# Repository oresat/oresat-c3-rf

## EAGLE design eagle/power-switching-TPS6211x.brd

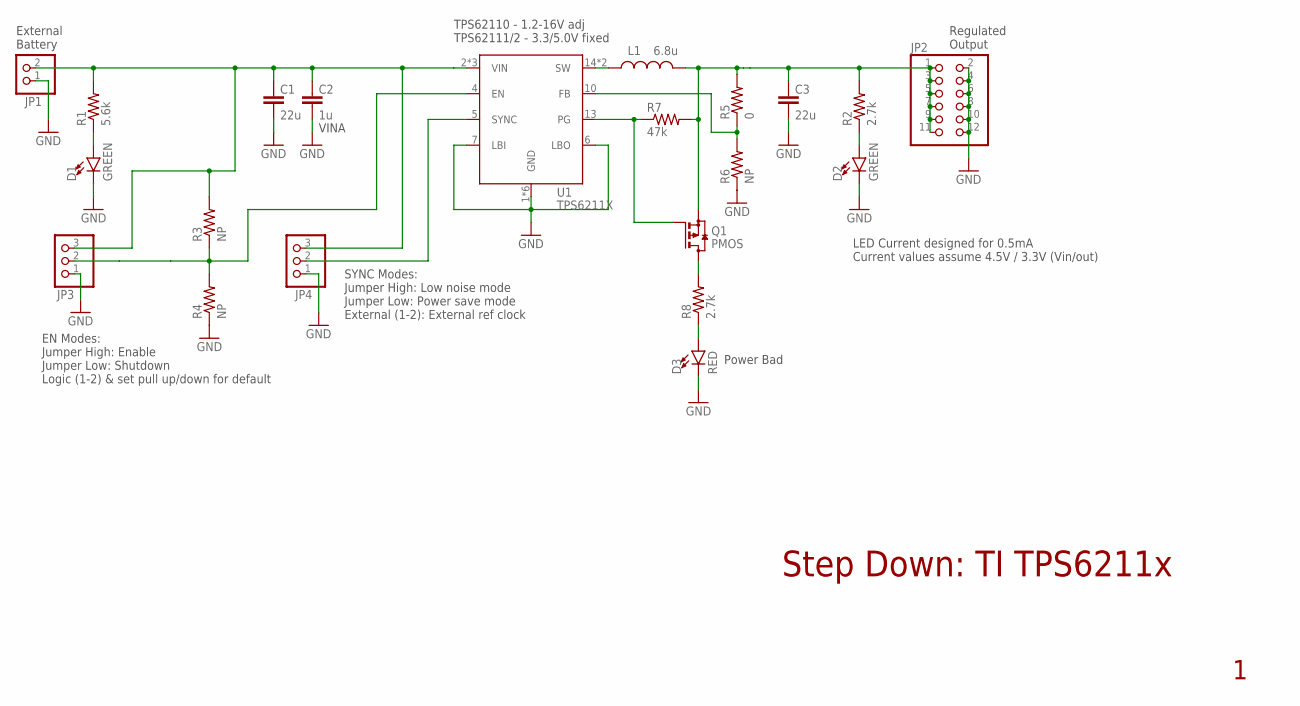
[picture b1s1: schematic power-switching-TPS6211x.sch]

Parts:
C1, C3: 22u; 1206-B
C2: 1u; .0603-B-NOSILK
D1, D2: GREEN; LED-0603
D3: RED; LED-0603
JP1: PINHD-1X2; 1X02
JP2: PINHD-2X6; 2X06
JP3, JP4: PINHD-1X3; 1X03
L1: 6.8u; ECS-MPI4040; MPN ECS-MPI4040R4-6R8-R
Q1: PMOS; SOT23
R1: 5.6k; .0603-B-NOSILK
R2, R8: 2.7k; .0603-B-NOSILK
R3, R4, R6: NP; .0402-B-NOSILK
R5: 0; .0402-B-NOSILK
R7: 47k; .0402-B-NOSILK
U1: TPS6211X; S-PVQFN-16

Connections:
+VIN: C1.1, C2.1, JP1.2, JP3.3, JP4.3, R1.2, R3.2, U1.2 (VIN), U1.3 (VIN), U1.8 (VIN)
+VOUT: C3.1, JP2.1, JP2.3, JP2.5, JP2.7, JP2.9, JP2.11, L1.2, Q1.2 (S), R2.2, R5.2, R7.2
+VOUT1: Q1.3 (D), R8.2
EN: JP3.2, R3.1, R4.2, U1.4 (EN)
FB: R5.1, R6.2, U1.10 (FB)
GND: C1.2, C2.2, C3.2, D1.C, D2.C, D3.C, JP1.1, JP2.2, JP2.4, JP2.6, JP2.8, JP2.10, JP2.12, JP3.1, JP4.1, R4.1, R6.1, U1.1 (GND), U1.6 (LBO), U1.7 (LBI), U1.9 (GND), U1.11 (GND), U1.12 (GND), U1.16 (GND), U1.PAD (GND)
unnamed: D3.A, R8.1
unnamed: D1.A, R1.1
unnamed: D2.A, R2.1
PG: Q1.1 (G), R7.1, U1.13 (PG)
SW: L1.1, U1.14 (SW), U1.15 (SW)
SYNC: JP4.2, U1.5 (SYNC)

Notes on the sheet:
Step Down: TI TPS6211x
Regulated Output
External Battery
SYNC Modes: Jumper High: Low noise mode Jumper Low: Power save mode External (1-2): External ref clock
EN Modes: Jumper High: Enable Jumper Low: Shutdown Logic (1-2) & set pull up/down for default
Power Bad
LED Current designed for 0.5mA Current values assume 4.5V / 3.3V (Vin/out)
VINA
TPS62110 - 1.2-16V adj TPS62111/2 - 3.3/5.0V fixed

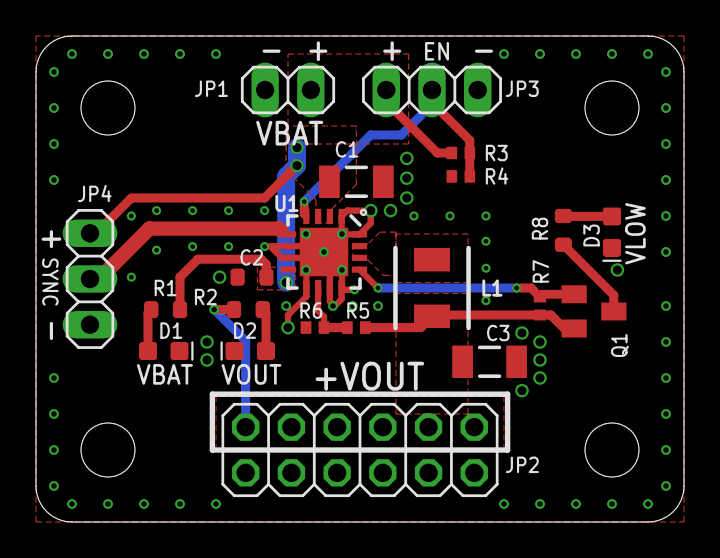
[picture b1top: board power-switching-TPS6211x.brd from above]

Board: 2 copper layers, 36.0 x 27.0 mm, 21 parts (0 on the bottom side), 12 nets.

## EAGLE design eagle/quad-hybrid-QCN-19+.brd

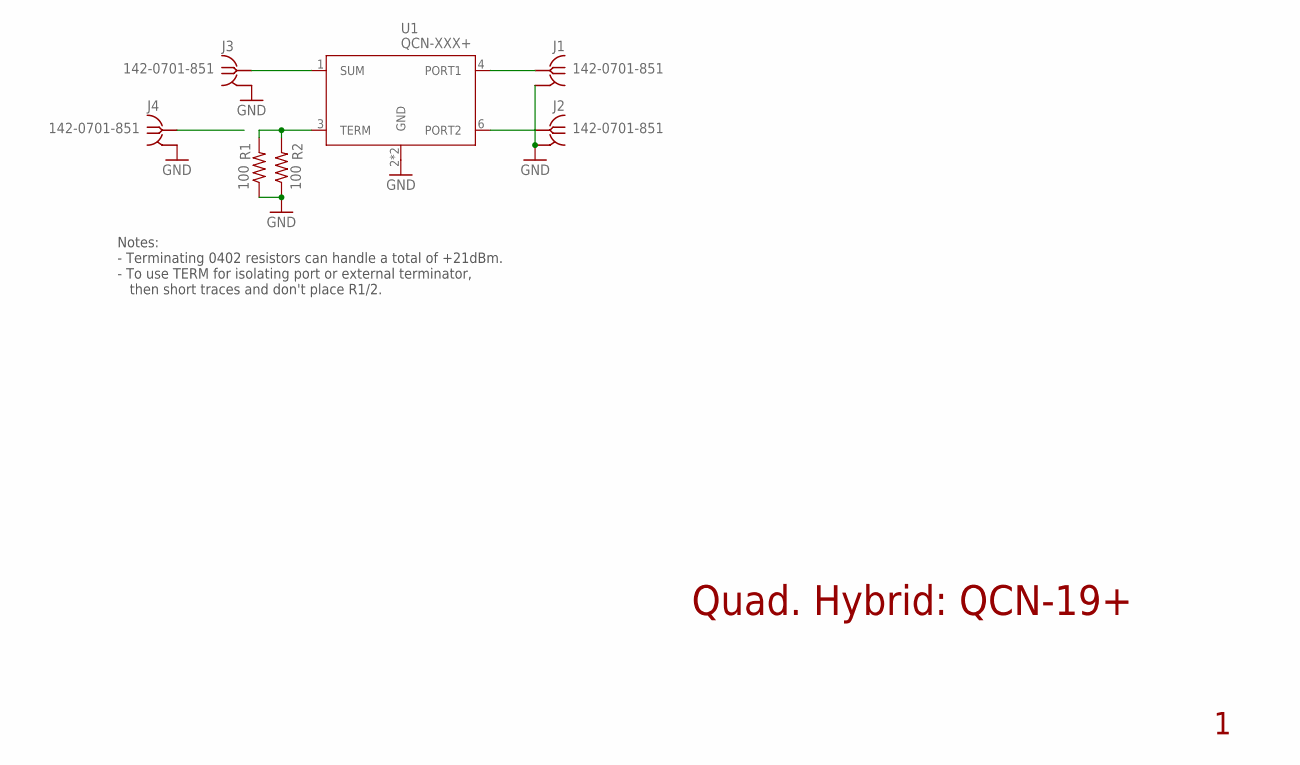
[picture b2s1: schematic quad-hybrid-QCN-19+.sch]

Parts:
J1, J2, J3, J4: 142-0701-851
R1, R2: 100; .0402-C-NOSILK
U1: QCN-XXX+

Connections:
GND: J1.GND1 (GND), J1.GND2 (GND), J1.GND3 (GND), J1.GND4 (GND), J2.GND1 (GND), J2.GND2 (GND), J2.GND3 (GND), J2.GND4 (GND), J3.GND1 (GND), J3.GND2 (GND), J3.GND3 (GND), J3.GND4 (GND), J4.GND1 (GND), J4.GND2 (GND), J4.GND3 (GND), J4.GND4 (GND), R1.1, R2.1, U1.2 (GND), U1.5 (GND)
ISO: J4.RF1 (RF)
P1: J1.RF1 (RF), U1.4 (PORT1)
P2: J2.RF1 (RF), U1.6 (PORT2)
SUM: J3.RF1 (RF), U1.1 (SUM)
TERM: R1.2, R2.2, U1.3 (TERM)

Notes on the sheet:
Quad. Hybrid: QCN-19+
Notes: - Terminating 0402 resistors can handle a total of +21dBm. - To use TERM for isolating port or external terminator, then short traces and don't place R1/2.

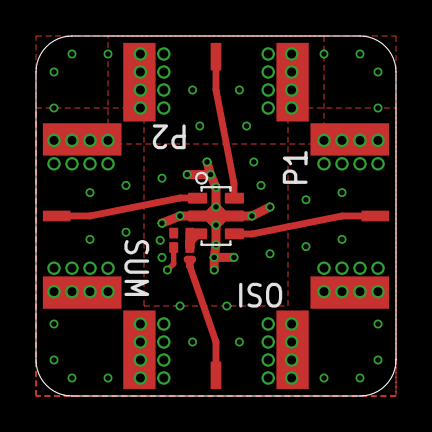
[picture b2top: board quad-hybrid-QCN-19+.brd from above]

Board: 4 copper layers, 20.0 x 20.0 mm, 7 parts (0 on the bottom side), 5 nets.

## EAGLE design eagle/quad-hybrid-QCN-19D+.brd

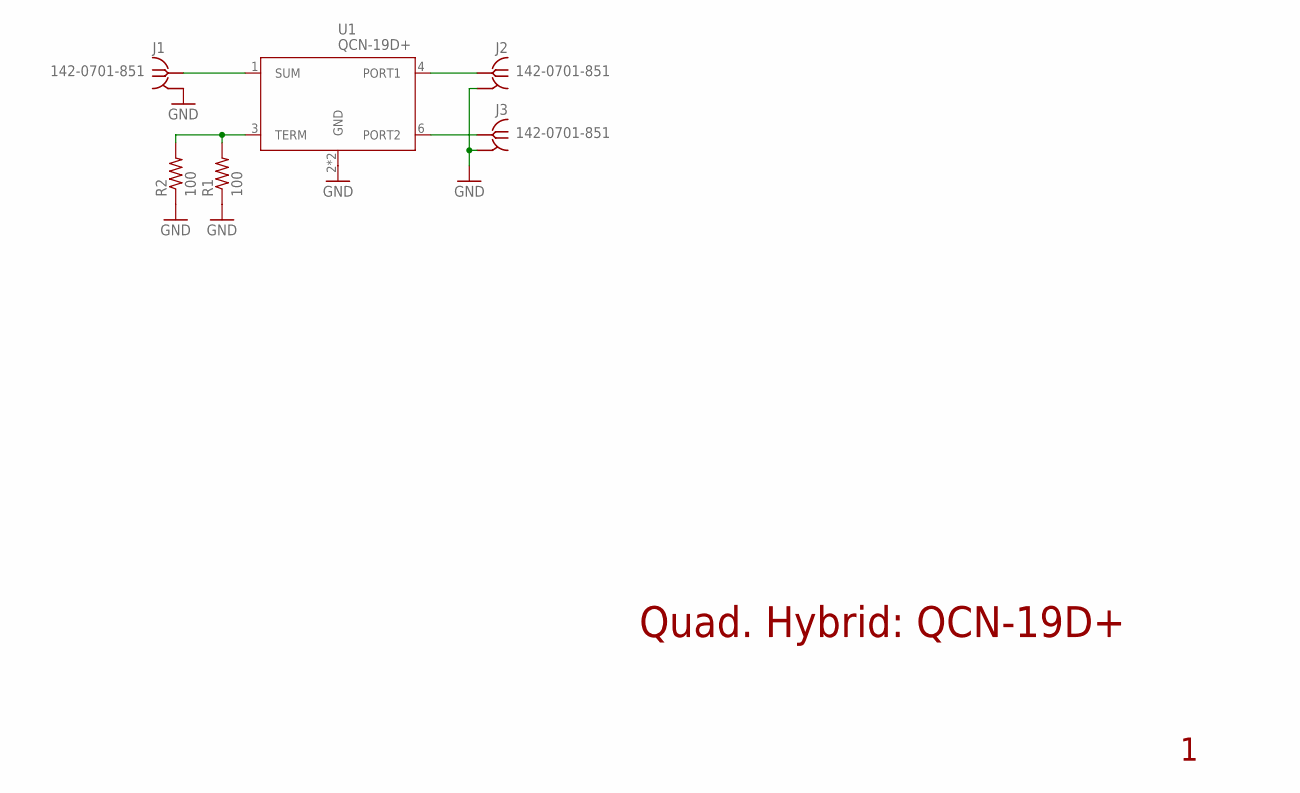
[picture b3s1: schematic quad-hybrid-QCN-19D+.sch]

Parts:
J1, J2, J3: 142-0701-851
R1, R2: 100; .0402-C-NOSILK
U1: QCN-19D+

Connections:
GND: J1.GND1 (GND), J1.GND2 (GND), J1.GND3 (GND), J1.GND4 (GND), J2.GND1 (GND), J2.GND2 (GND), J2.GND3 (GND), J2.GND4 (GND), J3.GND1 (GND), J3.GND2 (GND), J3.GND3 (GND), J3.GND4 (GND), R1.1, R2.1, U1.2 (GND), U1.5 (GND)
PORT1: J2.RF1 (RF), U1.4 (PORT1)
PORT2: J3.RF1 (RF), U1.6 (PORT2)
SUM: J1.RF1 (RF), U1.1 (SUM)
TERM: R1.2, R2.2, U1.3 (TERM)

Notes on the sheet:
Quad. Hybrid: QCN-19D+

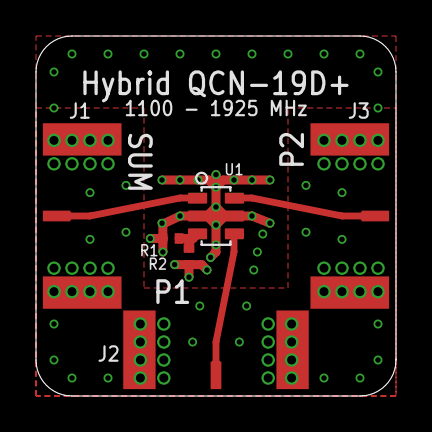
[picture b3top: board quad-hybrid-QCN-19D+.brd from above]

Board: 4 copper layers, 20.0 x 20.0 mm, 6 parts (0 on the bottom side), 5 nets.

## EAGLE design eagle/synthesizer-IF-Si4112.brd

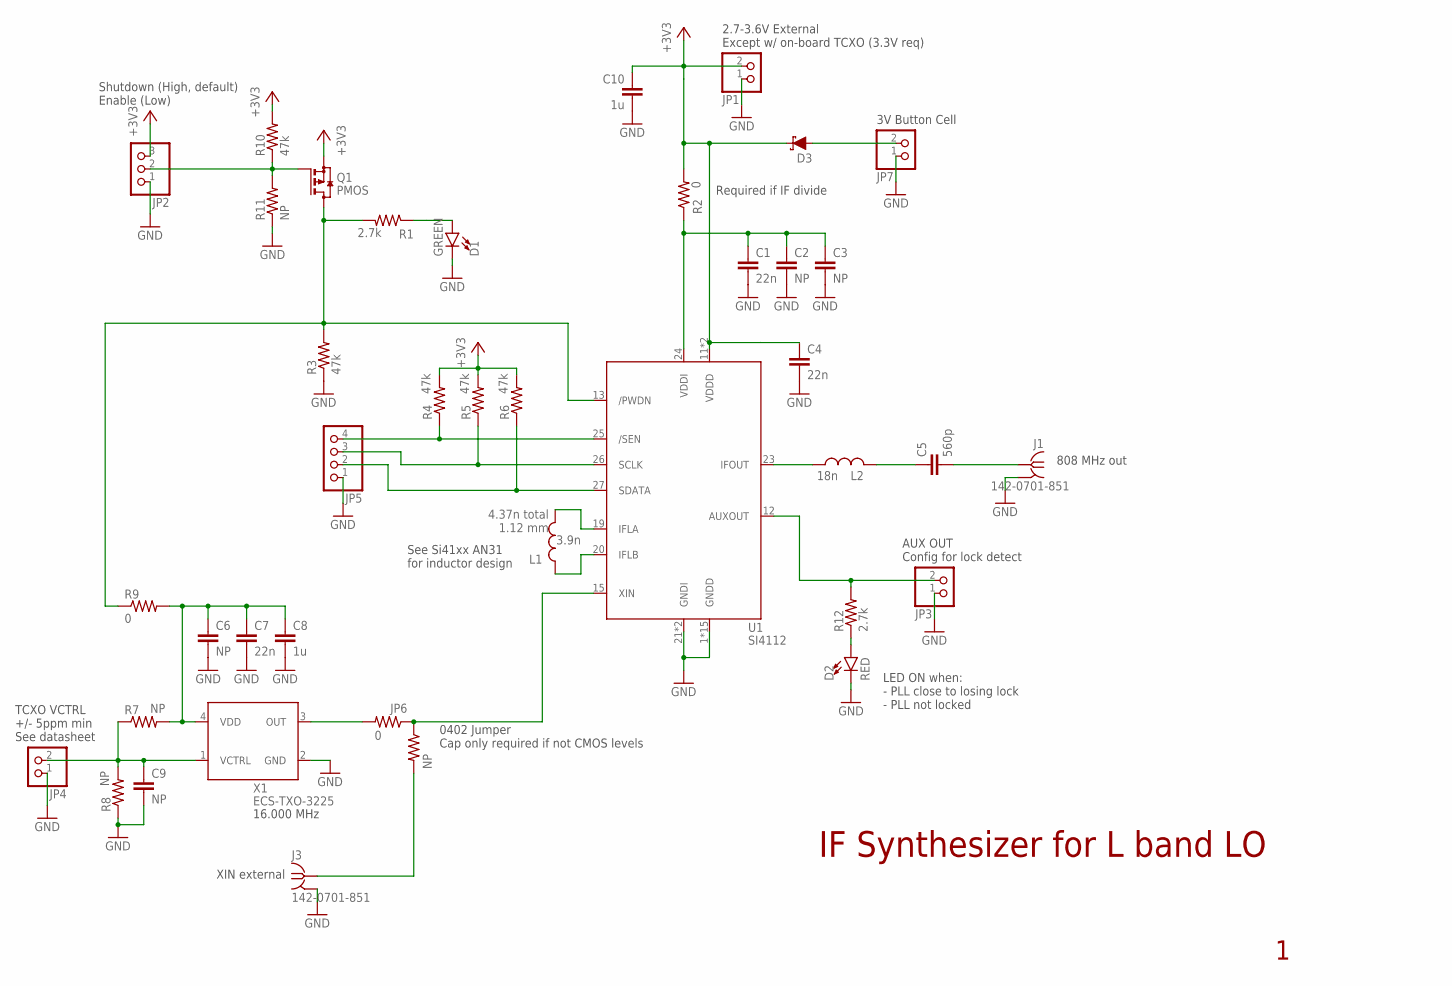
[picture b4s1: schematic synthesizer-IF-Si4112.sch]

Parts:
C1, C4, C7: 22n; .0603-B-NOSILK
C2, C3, C6, C9: NP; .0603-B-NOSILK
C5: 560p; .0402-B-NOSILK
C8, C10: 1u; .0603-B-NOSILK
D1: GREEN; LED-0603
D2: RED; LED-0603
D3: 120mA/40V/370mV; SOD-523
J1, J3: 142-0701-851
JP1, JP3, JP4, JP7: PINHD-1X2; 1X02
JP2: PINHD-1X3; 1X03
JP5: PINHD-1X4; 1X04
JP6: 0; .0402-B-NOSILK
L1: 3.9n; .0402-C-NOSILK
L2: 18n; .0402-B-NOSILK
Q1: PMOS; SOT23
R1, R12: 2.7k; .0603-B-NOSILK
R2, R9: 0; .0603-B-NOSILK
R3, R4, R5, R6, R10: 47k; .0402-B-NOSILK
R7, R8: NP; .0603-B-NOSILK
R11, R99: NP; .0402-B-NOSILK
U1: SI4112; QFN28-5X5-WITH-CENTER-PAD
X1: ECS-TXO-3225; 3.2X2.5

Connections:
+3V3: C4.1, C10.1, D3.C, JP1.2, JP2.3, Q1.2 (S), R2.2, R4.2, R5.2, R6.2, R10.2, U1.11 (VDDD), U1.17 (VDDD)
/SEN: JP5.4, R4.1, U1.25 (/SEN)
AUX: JP3.2, R12.2, U1.12 (AUXOUT)
GND: C1.2, C2.2, C3.2, C4.2, C6.2, C7.2, C8.2, C9.2, C10.2, D1.C, D2.C, J1.GND1 (GND), J1.GND2 (GND), J1.GND3 (GND), J1.GND4 (GND), J3.GND1 (GND), J3.GND2 (GND), J3.GND3 (GND), J3.GND4 (GND), JP1.1, JP2.1, JP3.1, JP4.1, JP5.1, JP7.1, R3.1, R8.1, R11.1, U1.1 (GNDD), U1.2 (GNDD), U1.3 (GNDD), U1.4 (GNDD), U1.5 (GNDD), U1.6 (GNDD), U1.7 (GNDD), U1.8 (GNDD), U1.9 (GNDD), U1.10 (GNDD), U1.14 (GNDD), U1.16 (GNDD), U1.18 (GNDD), U1.21 (GNDI), U1.22 (GNDI), U1.28 (GNDD), U1.PAD (GNDD), X1.2 (GND)
IF_OUT: C5.2, J1.RF1 (RF)
unnamed: D3.A, JP7.2
unnamed: L1.2, U1.19 (IFLA)
unnamed: L1.1, U1.20 (IFLB)
unnamed: JP2.2, Q1.1 (G), R10.1, R11.2
unnamed: Q1.3 (D), R1.2, R3.2, R9.1, U1.13 (/PWDN)
unnamed: JP6.2, X1.3 (OUT)
unnamed: C6.1, C7.1, C8.1, R7.2, R9.2, X1.4 (VDD)
unnamed: C5.1, L2.2
unnamed: D1.A, R1.1
unnamed: D2.A, R12.1
unnamed: L2.1, U1.23 (IFOUT)
unnamed: C1.1, C2.1, C3.1, R2.1, U1.24 (VDDI)
REF_IN: J3.RF1 (RF), R99.2
SCLK: JP5.3, R5.1, U1.26 (SCLK)
SDATA: JP5.2, R6.1, U1.27 (SDATA)
VCTRL: C9.1, JP4.2, R7.1, R8.2, X1.1 (VCTRL)
XIN: JP6.1, R99.1, U1.15 (XIN)

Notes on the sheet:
IF Synthesizer for L band LO
4.37n total 1.12 mm
Required if IF divide
808 MHz out
XIN external
2.7-3.6V External Except w/ on-board TCXO (3.3V req)
16.000 MHz
0402 Jumper Cap only required if not CMOS levels
Shutdown (High, default) Enable (Low)
TCXO VCTRL +/- 5ppm min See datasheet
AUX OUT Config for lock detect
LED ON when: - PLL close to losing lock - PLL not locked
3V Button Cell
See Si41xx AN31 for inductor design

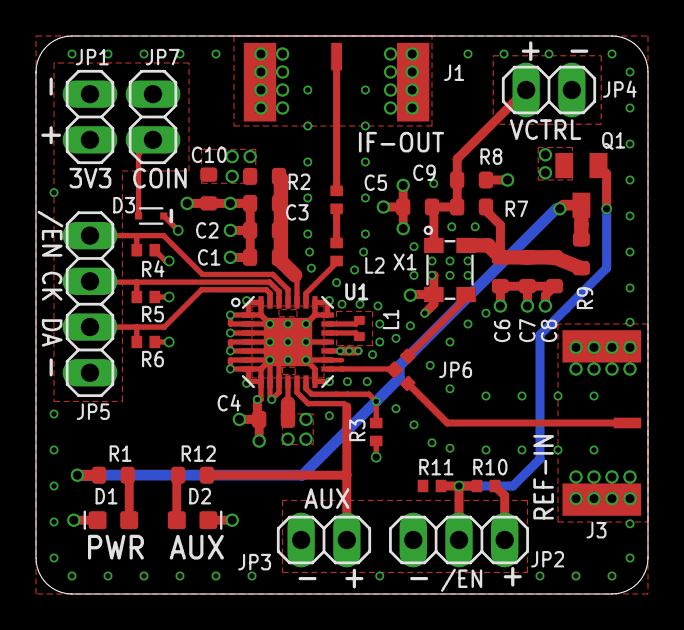
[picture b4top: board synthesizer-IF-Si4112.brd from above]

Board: 4 copper layers, 34.0 x 31.0 mm, 40 parts (0 on the bottom side), 22 nets.

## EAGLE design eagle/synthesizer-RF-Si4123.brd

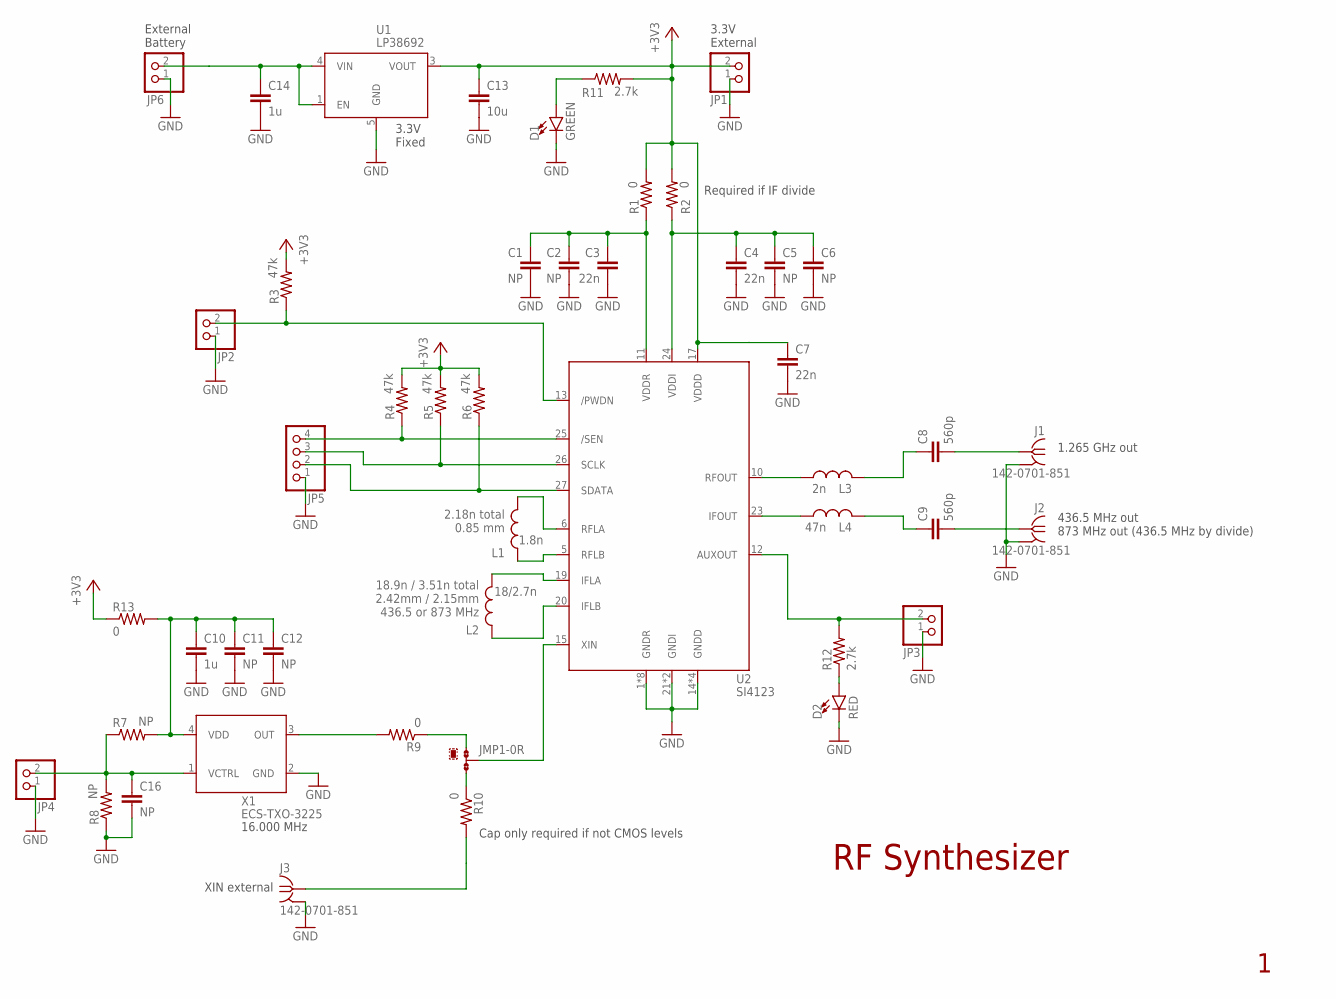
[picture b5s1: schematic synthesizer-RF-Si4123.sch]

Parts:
C1, C2, C5, C6, C11, C12, C16: NP; .0603-B-NOSILK
C3, C4, C7: 22n; .0603-B-NOSILK
C8, C9: 560p; .0402-B-NOSILK
C10, C14: 1u; .0603-B-NOSILK
C13: 10u; .0805-B-NOSILK
D1: GREEN; LED-0603
D2: RED; LED-0603
J1, J2, J3: 142-0701-851
JMP1: 0R-JUMPA; A0R-JMP
JP1, JP2, JP3, JP4, JP6: PINHD-1X2; 1X02
JP5: PINHD-1X4; 1X04
L1: 1.8n; .0402-C-NOSILK
L2: 18/2.7n; .0402-C-NOSILK
L3: 2n; .0402-B-NOSILK
L4: 47n; .0402-B-NOSILK
R1, R2, R13: 0; .0603-B-NOSILK
R3, R4, R5, R6: 47k; .0402-B-NOSILK
R7, R8: NP; .0603-B-NOSILK
R9, R10: 0; .0402-B-NOSILK
R11, R12: 2.7k; .0603-B-NOSILK
U1: LP38692; SOT223-5
U2: SI4123; QFN28-5X5-WITH-CENTER-PAD
X1: ECS-TXO-3225; 3.2X2.5

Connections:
+3V3: C7.1, C13.1, JP1.2, R1.2, R2.2, R3.2, R4.2, R5.2, R6.2, R11.2, R13.1, U1.3 (VOUT), U2.17 (VDDD)
+BAT: C14.1, JP6.2, U1.1 (EN), U1.4 (VIN)
GND: C1.2, C2.2, C3.2, C4.2, C5.2, C6.2, C7.2, C10.2, C11.2, C12.2, C13.2, C14.2, C16.2, D1.C, D2.C, J1.GND1 (GND), J1.GND2 (GND), J1.GND3 (GND), J1.GND4 (GND), J2.GND1 (GND), J2.GND2 (GND), J2.GND3 (GND), J2.GND4 (GND), J3.GND1 (GND), J3.GND2 (GND), J3.GND3 (GND), J3.GND4 (GND), JP1.1, JP2.1, JP3.1, JP4.1, JP5.1, JP6.1, R8.1, U1.5 (GND), U2.1 (GNDR), U2.2 (GNDR), U2.3 (GNDR), U2.4 (GNDR), U2.7 (GNDR), U2.8 (GNDR), U2.9 (GNDR), U2.14 (GNDD), U2.16 (GNDD), U2.18 (GNDD), U2.21 (GNDI), U2.22 (GNDI), U2.28 (GNDR), U2.PAD (GNDD), X1.2 (GND)
IF_OUT: C9.2, J2.RF1 (RF)
unnamed: JMP1.3, R10.1
unnamed: L1.2, U2.6 (RFLA)
unnamed: L1.1, U2.5 (RFLB)
unnamed: JP2.2, R3.1, U2.13 (/PWDN)
unnamed: JP5.4, R4.1, U2.25 (/SEN)
unnamed: JP5.3, R5.1, U2.26 (SCLK)
unnamed: JP5.2, R6.1, U2.27 (SDATA)
unnamed: JP3.2, R12.2, U2.12 (AUXOUT)
unnamed: JMP1.1, R9.1
unnamed: C10.1, C11.1, C12.1, R7.2, R13.2, X1.4 (VDD)
unnamed: C9.1, L4.2
unnamed: L4.1, U2.23 (IFOUT)
unnamed: C8.1, L3.2
unnamed: C1.1, C2.1, C3.1, R1.1, U2.11 (VDDR)
unnamed: JMP1.2, U2.15 (XIN)
unnamed: C16.1, JP4.2, R7.1, R8.2, X1.1 (VCTRL)
unnamed: R9.2, X1.3 (OUT)
unnamed: D1.A, R11.1
unnamed: D2.A, R12.1
unnamed: L2.2, U2.19 (IFLA)
unnamed: L2.1, U2.20 (IFLB)
unnamed: L3.1, U2.10 (RFOUT)
unnamed: C4.1, C5.1, C6.1, R2.1, U2.24 (VDDI)
REF_IN: J3.RF1 (RF), R10.2
RF_OUT: C8.2, J1.RF1 (RF)

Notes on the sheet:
RF Synthesizer
2.18n total 0.85 mm
Required if IF divide
Cap only required if not CMOS levels
1.265 GHz out
436.5 MHz out 873 MHz out (436.5 MHz by divide)
XIN external
3.3V External
16.000 MHz
External Battery
3.3V Fixed
18.9n / 3.51n total 2.42mm / 2.15mm 436.5 or 873 MHz

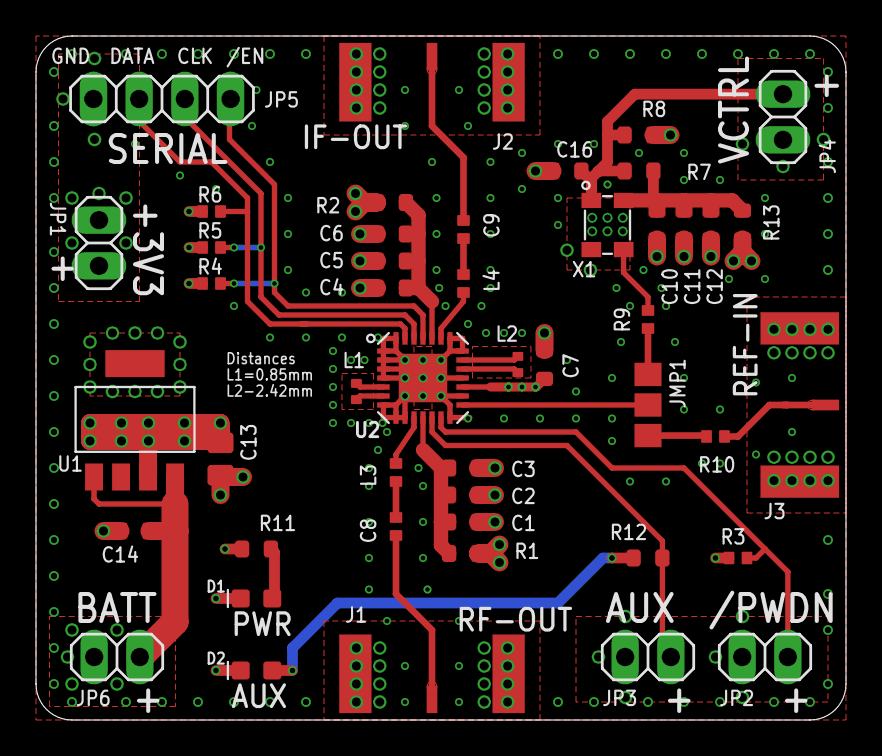
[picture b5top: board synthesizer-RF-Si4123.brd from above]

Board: 4 copper layers, 45.0 x 38.0 mm, 47 parts (0 on the bottom side), 29 nets.

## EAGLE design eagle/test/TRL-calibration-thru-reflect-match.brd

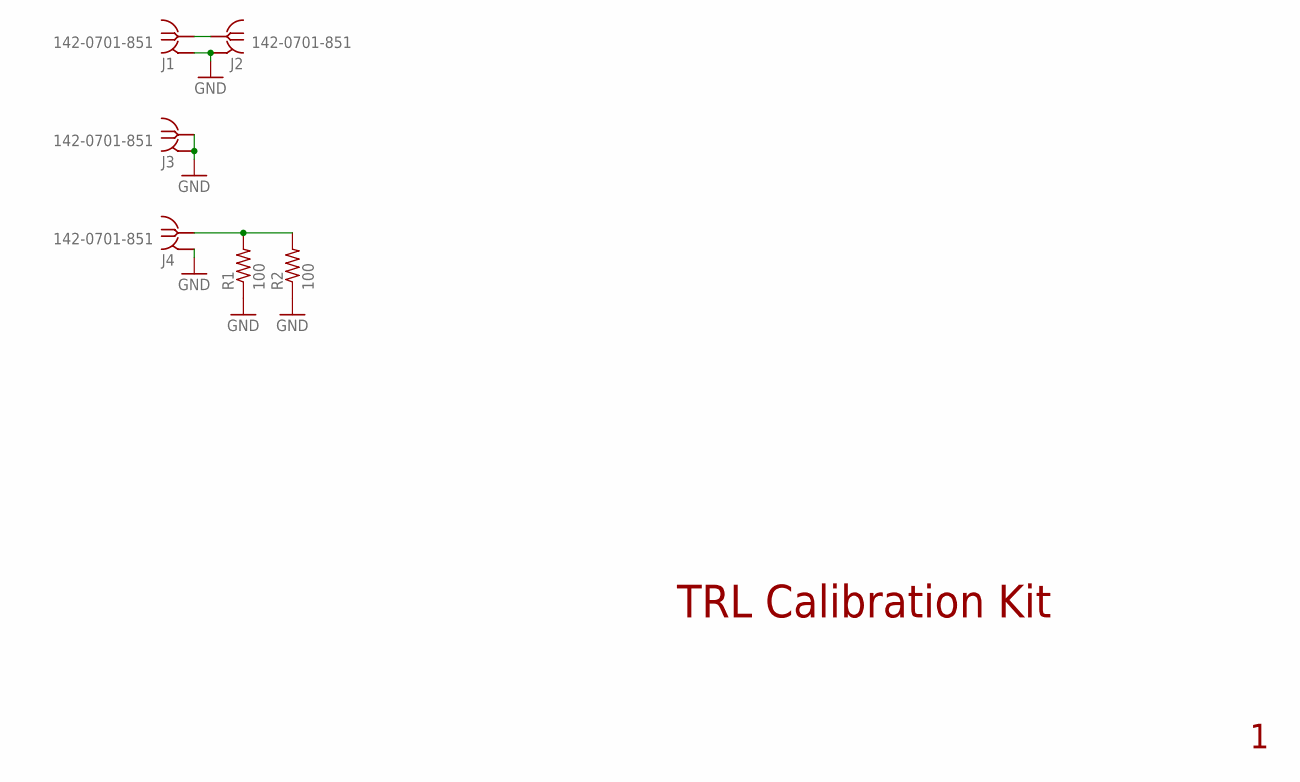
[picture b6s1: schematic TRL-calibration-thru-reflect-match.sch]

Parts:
J1, J2, J3, J4: 142-0701-851
R1, R2: 100; .0402-C-NOSILK

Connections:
GND: J1.GND1 (GND), J1.GND2 (GND), J1.GND3 (GND), J1.GND4 (GND), J2.GND1 (GND), J2.GND2 (GND), J2.GND3 (GND), J2.GND4 (GND), J3.GND1 (GND), J3.GND2 (GND), J3.GND3 (GND), J3.GND4 (GND), J3.RF1 (RF), J4.GND1 (GND), J4.GND2 (GND), J4.GND3 (GND), J4.GND4 (GND), R1.1, R2.1
MATCH: J4.RF1 (RF), R1.2, R2.2
THRU: J1.RF1 (RF), J2.RF1 (RF)

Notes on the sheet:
TRL Calibration Kit

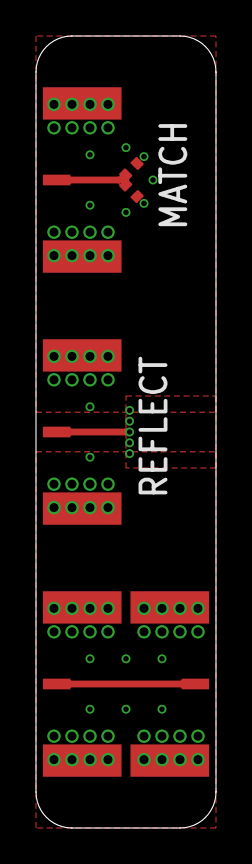
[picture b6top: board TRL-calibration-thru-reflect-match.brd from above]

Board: 4 copper layers, 10.0 x 44.0 mm, 6 parts (0 on the bottom side), 3 nets.

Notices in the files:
parts and their libraries:
SparkFun-LED: Licensing: Creative Commons ShareAlike 4.0 International - https://creativecommons.org/licenses/by-sa/4.0
